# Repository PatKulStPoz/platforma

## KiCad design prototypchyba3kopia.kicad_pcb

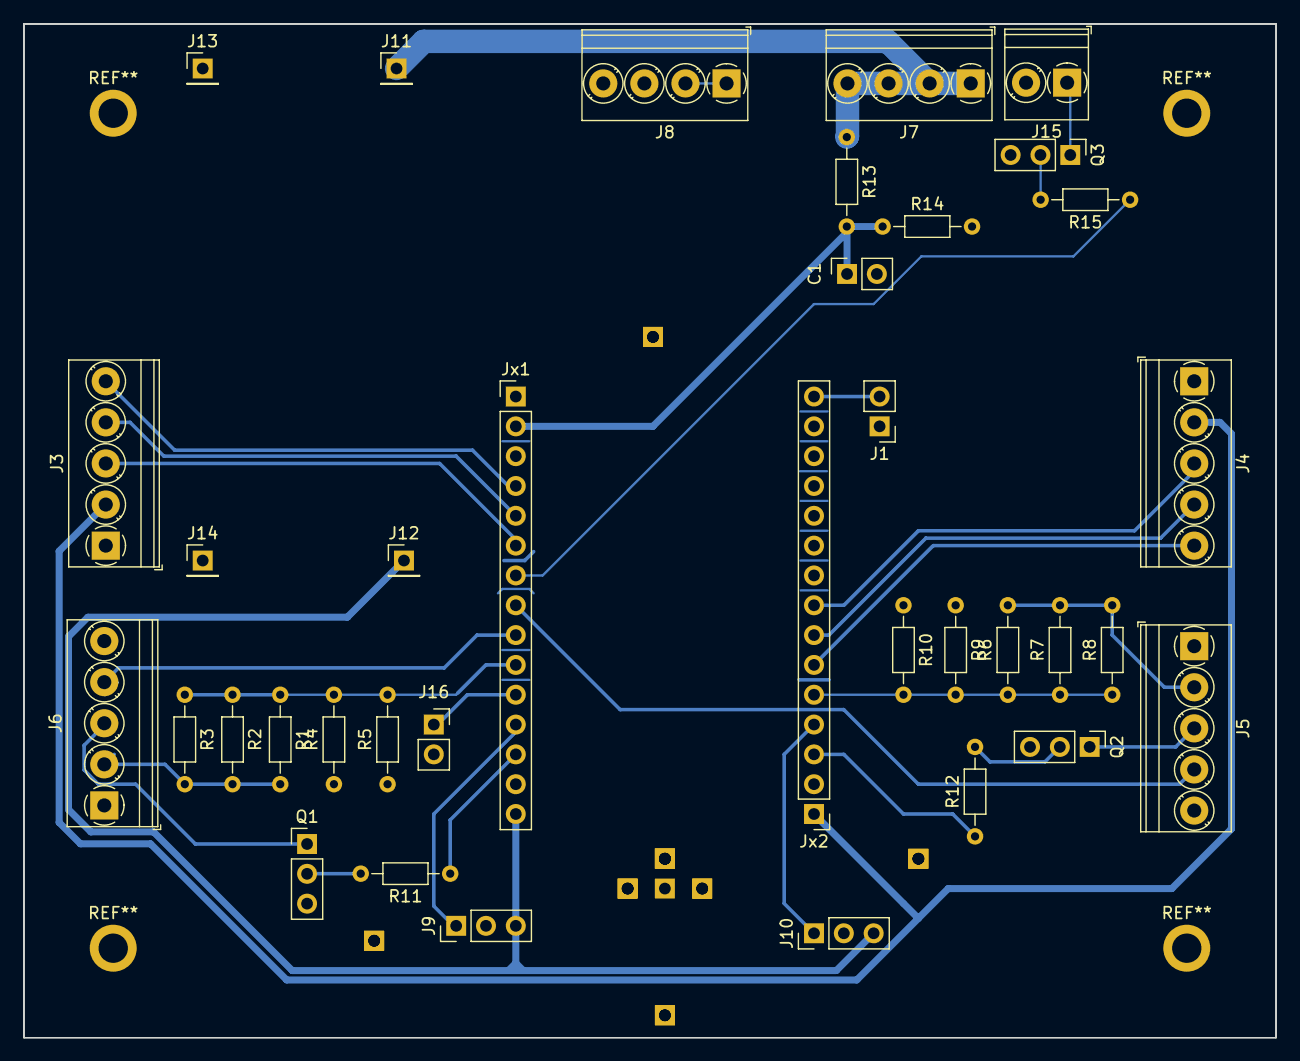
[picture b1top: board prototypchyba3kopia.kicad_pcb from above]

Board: 2 copper layers, 106.7 x 86.4 mm, 36 parts (0 on the bottom side), 29 nets.

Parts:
C1: C; PinSocket_1x02_P2.54mm_Vertical
J1: Conn_01x02_Pin; PinHeader_1x02_P2.54mm_Vertical
J3: hall lewy; TerminalBlock_Phoenix_PT-1,5-5-3.5-H_1x05_P3.50mm_Horizontal
J4: hall prawy; TerminalBlock_Phoenix_PT-1,5-5-3.5-H_1x05_P3.50mm_Horizontal
J5: plytka prawe kolo; TerminalBlock_Phoenix_PT-1,5-5-3.5-H_1x05_P3.50mm_Horizontal
J6: plytka lewe kolo; TerminalBlock_Phoenix_PT-1,5-5-3.5-H_1x05_P3.50mm_Horizontal
J7: +18V; TerminalBlock_Phoenix_PT-1,5-4-3.5-H_1x04_P3.50mm_Horizontal
J8: GND; TerminalBlock_Phoenix_PT-1,5-4-3.5-H_1x04_P3.50mm_Horizontal
J9: serwo lewy; PinHeader_1x03_P2.54mm_Vertical
J10: serwo prawy; PinHeader_1x03_P2.54mm_Vertical
J11: in+; PinHeader_1x01_P2.54mm_Vertical
J12: out+; PinHeader_1x01_P2.54mm_Vertical
J13: in-; PinHeader_1x01_P2.54mm_Vertical
J14: out-; PinHeader_1x01_P2.54mm_Vertical
J15: kogut; TerminalBlock_Phoenix_PT-1,5-2-3.5-H_1x02_P3.50mm_Horizontal
J16: led stan; PinSocket_1x02_P2.54mm_Vertical
Jx1, Jx2: Conn_01x15_Socket; PinHeader_1x15_P2.54mm_Vertical
Q1, Q2, Q3: Q_NPN_CBE; PinHeader_1x03_P2.54mm_Vertical
R1, R2, R3, R4, R5, R6, R7, R8, R9, R10, R11, R12, R13, R14, R15: R; R_Axial_DIN0204_L3.6mm_D1.6mm_P7.62mm_Horizontal

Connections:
+3V: J3.2, J4.2, Jx2.1
+5V: J9.3, J10.3, J12.1, Jx1.15
/HP5: J4.5, Jx2.6
/VP: C1.1, Jx1.2, R13.2, R14.1
GND: C1.2, J1.1, J3.1, J4.1, J5.5, J6.5, J7.1, J7.2, J7.3, J7.4, J8.1, J8.2, J8.3, J8.4, J9.2, J10.2, J11.1, J13.1, J14.1, J16.2, Jx1.14, Jx2.2, Q1.3 (E), Q2.3 (E), Q3.3 (E), R4.1, R5.1, R9.1, R10.1, R13.1, R14.2
unnamed: J1.2, Jx2.15
unnamed: J3.3, Jx1.6
unnamed: J3.4, Jx1.5
unnamed: J3.5, Jx1.4
unnamed: J4.3, Jx2.8
unnamed: J4.4, Jx2.7
unnamed: J5.2, R6.2, R7.2, R8.2
unnamed: J5.3, Q2.1 (C)
unnamed: J5.4, Jx1.8
unnamed: J6.2, R1.2, R2.2, R3.2
unnamed: J6.3, Q1.1 (C)
unnamed: J6.4, Jx1.9
unnamed: J9.1, Jx1.12
unnamed: J10.1, Jx2.4
unnamed: J15.1, Q3.1 (C)
unnamed: J16.1, Jx1.11
unnamed: Jx1.7, R15.1
unnamed: Jx1.10, R1.1, R2.1, R3.1, R4.2, R5.2
unnamed: Jx1.13, R11.1
unnamed: Jx2.3, R12.1
unnamed: Jx2.5, R6.1, R7.1, R8.1, R9.2, R10.2
unnamed: Q1.2 (B), R11.2
unnamed: Q2.2 (B), R12.2
unnamed: Q3.2 (B), R15.2

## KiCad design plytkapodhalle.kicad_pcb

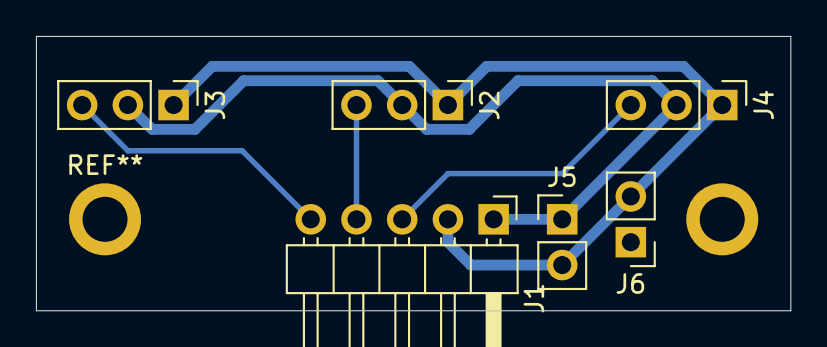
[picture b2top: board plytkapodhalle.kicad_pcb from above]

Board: 2 copper layers, 41.9 x 15.2 mm, 6 parts (0 on the bottom side), 5 nets.

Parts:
J1: Conn_01x05_Pin; PinHeader_1x05_P2.54mm_Horizontal
J2, J3, J4: Conn_01x03_Pin; PinHeader_1x03_P2.54mm_Vertical
J5, J6: Conn_01x02_Pin; PinHeader_1x02_P2.54mm_Vertical

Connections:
GND: J1.1, J2.2, J3.2, J4.2, J5.1, J6.1
unnamed: J1.3, J4.3
unnamed: J1.4, J2.3
unnamed: J1.5, J3.3
VCC: J1.2, J2.1, J3.1, J4.1, J5.2, J6.2
